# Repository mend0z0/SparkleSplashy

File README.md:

## Latest update

``
Latest update, or process that is going through
``

# Project

Description...

## Category

__Home/Office Automation__

## Features

- 
- 
- 

## Tech Stack

### Hardware

- **MCU:** ATSAM4SD16BA
- **Connection:** 
- **PCB Layers:** 4Layers (None-controlled Impedance)
- **CAD:** KiCAD

### Firmware

- **OS:** FreeRTOS
- **Programming Language:** C
- **IDE:** Microchip Studio

### Application

- **IDE:** Qt6
- **Operating System:** Linux/Windows
- **Device:** Laptop

### Mechanical

- **CAD:** Solid Edge
- **Printing Method:** 3D Printing

## Block Diagrams

## Screenshots

### Hardware

#### CAD View

#### 3D_View

#### Assembled Hardware

### Application

## Demo

Insert gif or link to demo, it'll be my youtube channel

## LOGO

## Author

- [@Siavash Taher Parvar](https://www.linkedin.com/in/mend0z0)

## Support

[Support Link](https://github.com/sponsors/mend0z0)

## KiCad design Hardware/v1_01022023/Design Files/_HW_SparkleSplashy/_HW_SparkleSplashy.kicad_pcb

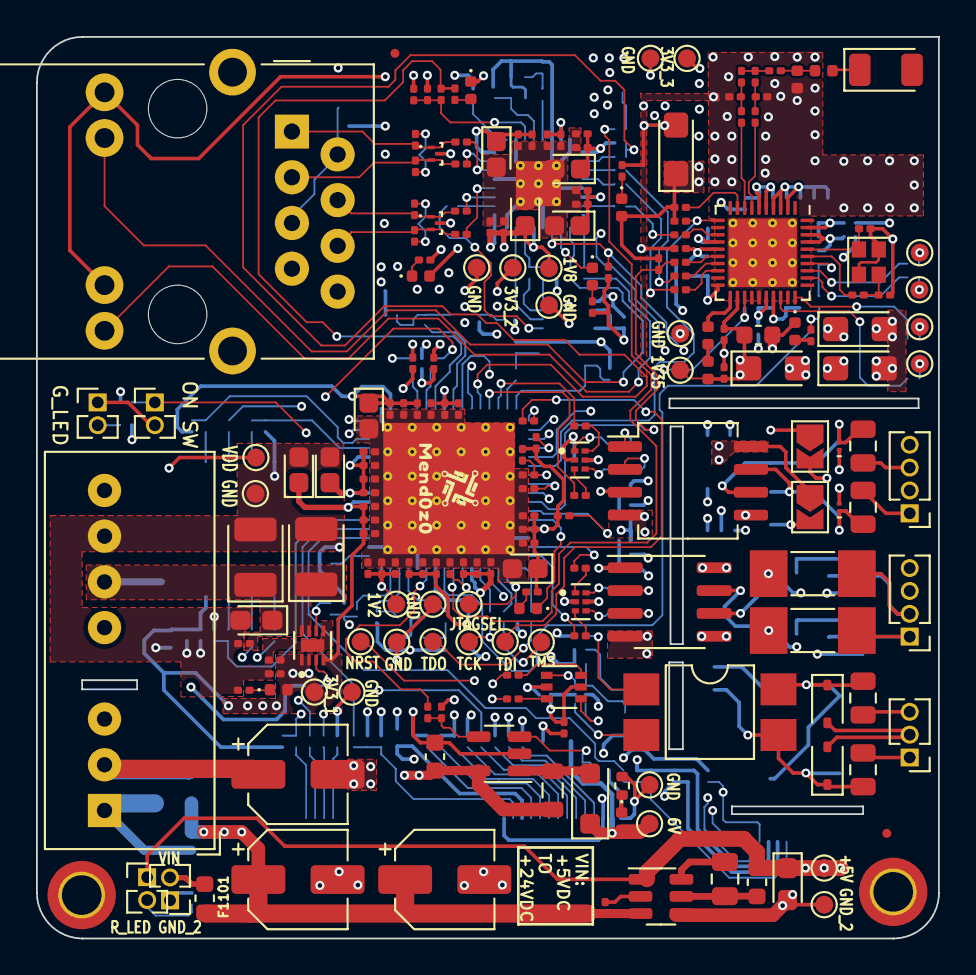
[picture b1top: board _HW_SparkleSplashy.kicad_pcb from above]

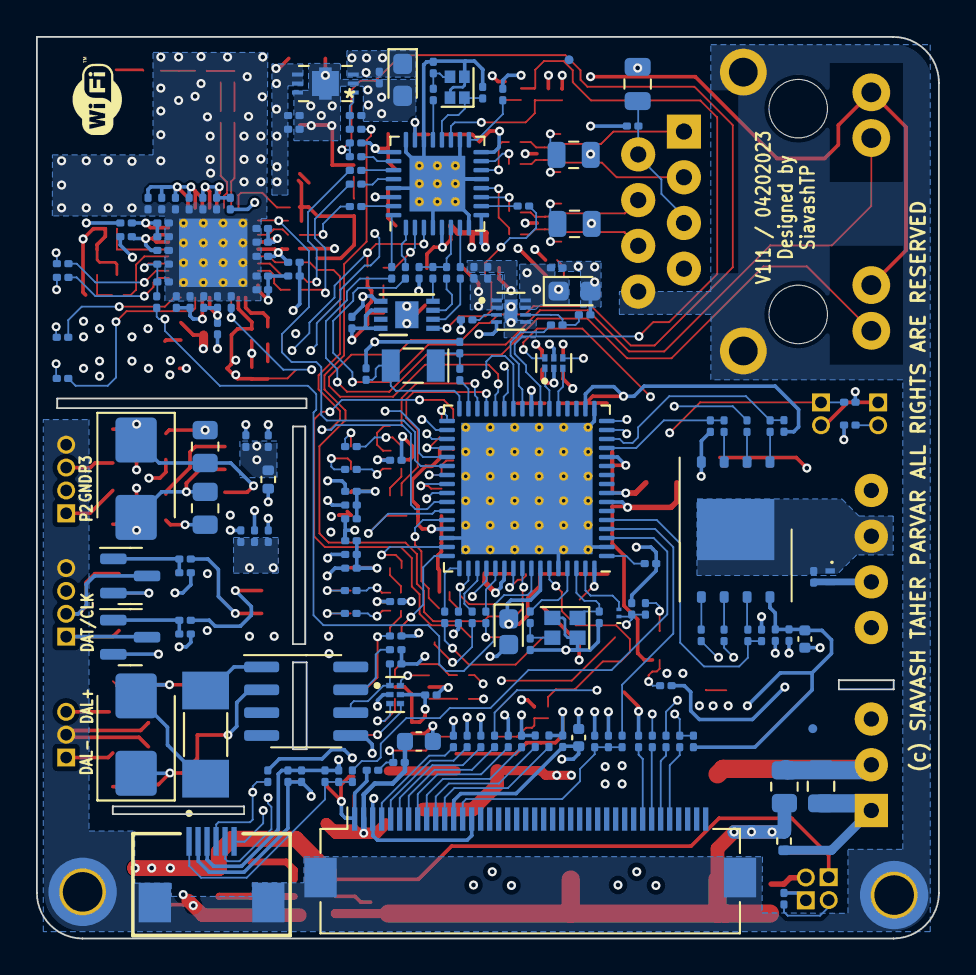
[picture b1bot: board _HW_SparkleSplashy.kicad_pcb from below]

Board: 4 copper layers, 50.1 x 50.1 mm, 381 parts (178 on the bottom side), 212 nets.

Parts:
ANT501: 2450AT18A100E; Johanson_2450AT18x100
C301, C302, C303, C304, C316, C317, C318, C324, C325, C332, C404, C408, C409, C410, C414, C504, C507, C508, C510, C520, C521, C524, C526, C529, C530, C603, C605, C803, C805, C1003, C1005, C1201, C1202, C1204, C1205: 100nF/6V3; C_0201_0603Metric
C305, C306, C307, C308, C326, C327, C328, C329, C405, C411, C412, C413, C415, C501, C514, C703: 10nF/6V3; C_0201_0603Metric
C309, C310, C311, C312: 1nF/50V; C_0201_0603Metric
C313, C314, C315, C319, C331, C417, C502, C505, C506, C509, C515, C516, C519, C525, C527, C528, C602, C801, C802, C804, C901, C902, C1001, C1002, C1004, C1206, C1207, C1208, C1209, C1210, C1211: 2u2F/6V3; C_0201_0603Metric
C320, C321, C322, C323, C406, C407, C522, C523: 12pF/50V; C_0201_0603Metric
C330: 470pF/50V; C_0201_0603Metric
C401: 10uF/50V; C_0805_2012Metric
C402, C403, C1101, C1102: 100nF/63V; C_0805_2012Metric
C416, C531, C601, C606, C702: 1uF/6V3; C_0201_0603Metric
C503, C511, C512: 1pF/50V; C_0201_0603Metric
C513, C1203, C1212: 10uF/16V; C_0603_1608Metric
C517, C518: 1p8F/50V; C_0201_0603Metric
C604, C701: 4u7F/6V3; C_0402_1005Metric
C1103: 100nF/16V; C_0201_0603Metric
D401, D402: RCLAMP0512TQTNT; 3-XDFN
D801: TISP4011H1BJR-S; D_SMB
D802, D803: ESDZV5H-1BU2; Nexperia_DSN0603-2_0.6x0.3mm_P0.4mm
D901: TISP4025H1BJR-S; D_SMB
D902, D903: SD22-01FTG; D_SOD-323
D1101: AQ1250-01ETG; SOD882
D1201: NSR01F30NXT5G; Nexperia_DSN0603-2_0.6x0.3mm_P0.4mm
D1202: 1N5819HW1-7-F; D_SOD-123F
EC1101, EC1102, EC1103: 10uF/50V; CP_Elec_5x5.3
F801, F802, F901, F902: 0805L010/24YR; Fuse_0805_2012Metric
F1101: ERB-RE1R00V; Fuse_0603_1608Metric
FD1301, FD1302, FD1303, FD1304: Fiducial_0.5mm_Mask1mm
J401: SI-60005-F; RJ45_Bel_SI-60062-F
J601: CF31401D0R0-05-NH; FPC_FH12-40S-0.5SH_1x40-1MP_P0.50mm_Horizontal
J602: F305-1A7H1-11006-E100; CONN_FPC_6POS_0.5P,BOTTOM
J801, J1001: FHDR_4POS_1.27MM; PinHeader_1x04_P1.27mm_Vertical
J901: FHDR_3POS_1.27MM; PinHeader_1x03_P1.27mm_Vertical
J1101, J1102, J1103, J1201: GRPB021VWVN-RC; PinHeader_1x02_P1.27mm_Vertical
JMP801, JMP802: JMP_2_OPEN; SolderJumper-2_P1.3mm_Open_TrianglePad1.0x1.5mm
L501: L-07C3N9SV6T; L_0402_1005Metric
L502: L-07C2N7SV6T; L_0402_1005Metric
L503, L504: WLCM0603TGB3N3TB; L_0201_0603Metric
L505: MLZ1005M2R2WT000; L_0402_1005Metric
L506: CW105550A-15NJ; L_0402_1005Metric
L1101: 4u7H; L_0603_1608Metric
L1201: 10uH; L_0805_2012Metric
LED301: ORANGE; LED_0402_1005Metric
LED302: RED; LED_0402_1005Metric
LED303, LED401: AMBER; LED_0402_1005Metric
LED1201, LED1202, LED1203: GREEN; LED_0402_1005Metric
LED1204: BLUE; LED_0402_1005Metric
MH1301, MH1302: MountingHole_2.2mm_M2_DIN965_Pad_TopBottom
Q1001, Q1002: 2N7002AQ-7; SOT-23
R301, R425, R427, R519, R601, R603, R604, R605, R606, R607, R608, R610, R611, R612, R613, R707, R708, R709, R1101, R1201, R1205, R1206, R1207, R1208, R1210: 10KR_1/20W; R_0201_0603Metric
R302, R303, R304, R305, R306, R903, R905: 3K3R_1/20W; R_0201_0603Metric
R307, R308, R309, R310, R311, R406, R506, R801, R802, R803, R804, R901, R902, R1001, R1002, R1003, R1004, R1007, R1008, R1211, R1212, R1213: 100R_1/20W; R_0201_0603Metric
R312, R313, R314, R408, R409, R426: 499R_1/20W; R_0201_0603Metric
R315, R316, R418, R424: 4K7R_1/20W; R_0201_0603Metric
R401, R410, R411, R412, R413, R501, R502, R503, R504, R505: 0R_1/20W; R_0201_0603Metric
R402, R403, R404, R405: 49R9_1/20W; R_0201_0603Metric
R407: 3K01R_1/20W; R_0201_0603Metric
R414, R415, R416, R417, R420, R421, R422, R423, R509, R510, R511, R512, R609, R614, R615, R616, R617, R701, R702, R703, R704, R705, R706: 27R4_1/20W; R_0201_0603Metric
R419, R513, R602, R618: 100KR_1/20W; R_0201_0603Metric
R507, R508, R518, R520: 1MR_1/20W; R_0201_0603Metric
R514, R515, R516, R517, R1103, R1104, R1202, R1203, R1204, R1209: 1KR_1/20W; R_0201_0603Metric
R805, R1005, R1006: 10R_1/20W; R_0201_0603Metric
R806: 1R_1/4W; R_0402_1005Metric
R807, R808: 680R_1/8W; R_0805_2012Metric
R904: 820R_1/20W; R_0201_0603Metric
R906: 4K7R_1W; R_MELF_MMB-0207
R1009, R1011: 47KR_1/20W; R_0201_0603Metric
R1010, R1012: 1KR_1W; R_MELF_MMB-0207
R1102: 0.1R_1/2W; R_0805_2012Metric
R1214: 93K1R_1/20W; R_0201_0603Metric
R1215: 24KR_1/20W; R_0201_0603Metric
R1216: 330R_1/10W; R_0402_1005Metric
TC301, TC302, TC303, TC304, TC305, TC401, TC402, TC403, TC404: 47uF/6V3; CP_EIA-1608-08_AVX-J
TC501, TC502, TC503, TC504: 22uF/6V3; CP_EIA-3216-10_Kemet-I
TC1101, TC1102: 33uF/16V; CP_EIA-3528-21_Kemet-B
TC1103, TC1201, TC1202, TC1203: 47uF/10V; CP_EIA-2012-12_Kemet-R
TP301, TP302, TP303, TP304, TP305, TP306, TP307, TP308, TP309, TP401, TP402, TP501, TP502, TP503, TP504, TP505, TP506, TP1101, TP1102, TP1103, TP1104, TP1201, TP1202, TP1203, TP1204, TP1205, TP1206, TP1207, TP1208: TestPoint_Pad_D1.0mm
U301: ATSAM4SD16BA-MU; QFN-64-1EP_9x9mm_P0.5mm_EP7.3x7.3mm_ThermalVias
U302, U801, U902, U1001: SN74LVC2G17DRYR; 6-SON
U401: KSZ8851SNLI-TR; QFN-32-1EP_5x5mm_P0.5mm_EP3.1x3.1mm_ThermalVias
U402: AT93C46DY6-YH-E; DFN-8-1EP_3x2mm_P0.5mm_EP1.3x1.5mm
U501: ATWILC1000B-MU-Y; QFN-40-1EP_5x5mm_P0.4mm_EP3.8x3.8mm_ThermalVias
U701: W25N01GVZEIG; WSON-8-1EP_8x6mm_P1.27mm_EP3.4x4.3mm
U802: MAX22028AWA+; SO-8_5.3x6.2mm_P1.27mm
U901: NC7WZ14P6X-L22347; SOT-363_SC-70-6
U903: AQY212EHA; SMDIP-4_W7.62mm
U904: VO207AT; SOIC-8_3.9x4.9mm_P1.27mm
U1002: ISO7720FDR; SOIC-8_3.9x4.9mm_P1.27mm
U1101: AP63205WU-7; SOT-23-6
U1102: PRM3W-E12-S5-S; Converter_DCDC_XP_POWER-ITxxxxxS_THT
U1201: BD33IC0WHFV-GTR; 6HVSOF
U1202: AP3012KTR-G1; SOT-23-5
U1203, U1204: LD56100DPU33R; 8-DFN
VDR1101: B72590P8200S060; R_0402_1005Metric
X301: 16MHz/10ppm; Crystal_SMD_2016-4Pin_2.0x1.6mm
X302: 32.768 kHz/5ppm; Crystal_SMD_EuroQuartz_EQ161-2Pin_3.2x1.5mm
X401: 25MHz/10ppm; Crystal_4SMD_1216_4Pin_1.2X1.6mm
X501: 26MHz/10ppm; Crystal_SMD_2016-4Pin_2.0x1.6mm

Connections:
+1V35: C501.2, C502.1, C504.1, C509.1, C510.1, C513.1, C514.1, C519.1, C524.1, C525.1, C526.1, C527.1, C529.1, L505.1, TC501.1, TP501.1, U501.2 (VDD_RF_RX_1V3), U501.3 (VDD_AMS_1V3), U501.4 (VDD_RF_TX_1V3), U501.14 (VDDC_1V3), U501.22 (VREG_BUCK), U501.27 (VDDC_1V3), U501.37 (VDD_SXDIG_1V3), U501.38 (VDD_VCO_1V3)
+5V: J1102.1, L1101.2, R806.2, R1006.2, TC1103.1, TP1103.1, U1101.1 (FB)
+6V: C1212.2, D1202.1, J601.2, LED1204.2, R1214.2, TP1201.1
/BLOCK DIAGRAM/2.4" TFT LCD + TOUCH/CTP_RESET: C601.1, J602.1, R601.2, R602.1
/BLOCK DIAGRAM/2.4" TFT LCD + TOUCH/TFT_CLK: J601.35, R616.2
/BLOCK DIAGRAM/2.4" TFT LCD + TOUCH/TFT_D/C: J601.34, R615.2
/BLOCK DIAGRAM/2.4" TFT LCD + TOUCH/TFT_IM0: J601.4, R606.2
/BLOCK DIAGRAM/2.4" TFT LCD + TOUCH/TFT_IM1: J601.5, R607.2
/BLOCK DIAGRAM/2.4" TFT LCD + TOUCH/TFT_IM2: J601.6, R608.2
/BLOCK DIAGRAM/2.4" TFT LCD + TOUCH/TFT_RESET: C606.1, J601.13, R605.2, R618.1
/BLOCK DIAGRAM/2.4" TFT LCD + TOUCH/TFT_SDA: J601.7, R609.2
/BLOCK DIAGRAM/512MB SPI FLASH/CLK: R706.1, U701.6 (CLK)
/BLOCK DIAGRAM/512MB SPI FLASH/DI: R705.1, U701.5 (DI(IO0))
/BLOCK DIAGRAM/512MB SPI FLASH/DO: R704.1, U701.2 (DO(IO1))
/BLOCK DIAGRAM/512MB SPI FLASH/~CHIPSEL: R703.1, U701.1 (~CS)
/BLOCK DIAGRAM/512MB SPI FLASH/~HOLD: R702.1, U701.7 (~HOLD(IO3))
/BLOCK DIAGRAM/512MB SPI FLASH/~WP: R701.1, U701.3 (~WP(IO2))
/BLOCK DIAGRAM/+3V3_1: C301.2, C302.2, C303.2, C304.2, C305.2, C306.2, C307.2, C308.2, C309.2, C310.2, C311.2, C312.2, C331.2, C332.2, C602.2, C603.2, C604.2, C605.2, C701.2, C702.2, C703.2, C801.1, C901.1, C902.1, C1001.2, C1207.1, C1211.1, J601.12, J602.2, LED1203.2, R301.1, R313.2, R315.1, R316.1, R603.1, R604.2, R607.1, R608.1, R707.2, R805.1, R903.2, R904.2, R905.2, R1005.2, TC301.1, TC302.1, TC303.1, TC304.1, TP1207.1, U301.7 (VDDIN_3V3), U301.18 (VDDIO_3V3), U301.45 (VDDIO_3V3), U301.58 (VDDIO_3V3), U302.5 (VCC), U701.8 (VCC), U801.5 (VCC), U901.5 (VCC), U902.5 (VCC), U1001.5 (VCC), U1204.1 (VOUT), U1204.2 (VOUT), U1204.4 (FB)
/BLOCK DIAGRAM/+3V3_2: C404.1, C405.1, C409.1, C410.1, C412.1, C413.1, C417.1, C1206.1, C1210.1, J401.L1 (GA), J401.L3 (YA), LED1202.2, R401.1, R418.2, R424.1, R426.2, R427.1, TC401.1, TC403.1, TC404.1, TP1205.1, U401.16 (VDD_A3.3), U401.25 (VDD_IO), U401.30 (VDD_IO), U402.6 (ORG), U402.8 (VCC), U1203.1 (VOUT), U1203.2 (VOUT), U1203.4 (FB)
/BLOCK DIAGRAM/+3V3_3: C1208.1, C1209.1, LED1201.2, R501.1, R502.1, R503.1, R504.1, R505.1, R507.1, R518.1, R520.1, TC502.1, TC503.1, TC504.1, TP1203.1, U1201.1 (VO), U1201.2 (FB)
/BLOCK DIAGRAM/ATWIL_EN: R508.1, U301.26 (PA26/PGMD14), U501.23 (CHIP_EN)
/BLOCK DIAGRAM/ATWIL_IRNQ: R518.2, U301.38 (PA28), U501.11 (GPIO2/IRQN)
/BLOCK DIAGRAM/ATWIL_~CS: R509.2, R520.2, U301.42 (PA30)
/BLOCK DIAGRAM/ATWIL_~RST: R312.2, R519.1, U301.57 (DDP/PB11)
/BLOCK DIAGRAM/CTP_INT: J602.4, R604.1, U301.37 (PA27/PGMD15)
/BLOCK DIAGRAM/CTP_~RST: R601.1, U301.3 (PB0/AD4)
/BLOCK DIAGRAM/DALI_RX: R901.1, U301.35 (PA5/PGMRDY)
/BLOCK DIAGRAM/DALI_TX: R902.1, U301.34 (PA6/PGMNOE)
/BLOCK DIAGRAM/DMX_RX: R801.1, U301.30 (PA9/PGMM1)
/BLOCK DIAGRAM/DMX_TX: R802.1, U301.29 (PA10/PGMM2)
/BLOCK DIAGRAM/ETHERNET CONTROLLER/KSZ_1V8_OUT: C408.1, C411.1, C414.1, C415.1, TC402.1, TP401.1, U401.5 (VDD_CO1.8), U401.9 (VDD_A1.8), U401.23 (VDD_D1.8)
/BLOCK DIAGRAM/ETHERNET CONTROLLER/KSZ_CSN: R420.1, U401.26 (CSN)
/BLOCK DIAGRAM/ETHERNET CONTROLLER/KSZ_ISET: R407.2, U401.17 (ISET)
/BLOCK DIAGRAM/ETHERNET CONTROLLER/KSZ_LED0: J401.L2 (GK), R408.1
/BLOCK DIAGRAM/ETHERNET CONTROLLER/KSZ_LED1: J401.L4 (YK), R409.1
/BLOCK DIAGRAM/ETHERNET CONTROLLER/KSZ_RSTN: C416.1, R419.1, R425.2, U401.19 (RSTN)
/BLOCK DIAGRAM/ETHERNET CONTROLLER/KSZ_SCK: R423.1, U401.28 (SCLK)
/BLOCK DIAGRAM/ETHERNET CONTROLLER/KSZ_SI: R422.1, U401.31 (SI)
/BLOCK DIAGRAM/ETHERNET CONTROLLER/KSZ_SO: R421.1, U401.27 (SO)
/BLOCK DIAGRAM/ETHERNET CONTROLLER/KSZ_XTAL1: C406.2, U401.20 (X1), X401.1
/BLOCK DIAGRAM/ETHERNET CONTROLLER/KSZ_XTAL2: R406.2, U401.21 (X2)
/BLOCK DIAGRAM/I2C_SCL: J602.5, R315.2, U301.36 (PA4/PGMNCMD)
/BLOCK DIAGRAM/I2C_SDA: J602.6, R316.2, U301.43 (PA3)
/BLOCK DIAGRAM/ISOLATED DALI/DALI_+: F901.2, J901.3
/BLOCK DIAGRAM/ISOLATED DALI/DALI_-: F902.2, J901.1
/BLOCK DIAGRAM/ISOLATED DALI/DALI_BUFF_1A: R903.1, U902.1 (1A), U904.6 (C)
/BLOCK DIAGRAM/ISOLATED DALI/DALI_BUFF_1Y: R901.2, U901.6 (1Y)
/BLOCK DIAGRAM/ISOLATED DALI/DALI_BUFF_2A: R902.2, U901.3 (2A)
/BLOCK DIAGRAM/ISOLATED DALI/DALI_BUFF_2Y: U902.4 (2Y), U903.2
/BLOCK DIAGRAM/ISOLATED DCDC CONVERTER/AP05_BST: C1102.1, U1101.6 (BST)
/BLOCK DIAGRAM/ISOLATED DCDC CONVERTER/AP05_EN: R1101.2, U1101.2 (EN)
/BLOCK DIAGRAM/ISOLATED DCDC CONVERTER/AP05_SW: C1102.2, L1101.1, U1101.5 (SW)
/BLOCK DIAGRAM/ISOLATED DMX/DMX_BUFF_1A: R803.1, U801.1 (1A)
/BLOCK DIAGRAM/ISOLATED DMX/DMX_BUFF_1Y: R801.2, U801.6 (1Y)
/BLOCK DIAGRAM/ISOLATED DMX/DMX_BUFF_2A: R802.2, U801.3 (2A)
/BLOCK DIAGRAM/ISOLATED DMX/DMX_BUFF_2Y: R804.1, U801.4 (2Y)
/BLOCK DIAGRAM/ISOLATED DMX/MAX22028_A: D801.1, D803.2, F802.1, R808.2, U802.6 (A)
/BLOCK DIAGRAM/ISOLATED DMX/MAX22028_B: D801.2, D802.1, F801.1, R807.1, U802.7 (B)
/BLOCK DIAGRAM/ISOLATED DMX/MAX22028_RXD: R803.2, U802.1 (RXD)
/BLOCK DIAGRAM/ISOLATED DMX/MAX22028_TXD: R804.2, U802.2 (TXD)
/BLOCK DIAGRAM/ISOLATED DMX/MAX22028_VDDA: C802.2, C803.2, R805.2, U802.3 (VDDA)
/BLOCK DIAGRAM/ISOLATED DMX/MAX22028_VDDB: C804.1, C805.1, JMP801.1, R806.1, U802.8 (VDDB)
/BLOCK DIAGRAM/ISOLATED DMX/XLR_PIN2: F801.2, J801.1
/BLOCK DIAGRAM/ISOLATED DMX/XLR_PIN3: F802.2, J801.3
/BLOCK DIAGRAM/ISOLATED RGB CHIP/ISO7720_INA: R1003.2, U1002.2 (INA)
/BLOCK DIAGRAM/ISOLATED RGB CHIP/ISO7720_INB: R1004.2, U1002.3 (INB)
/BLOCK DIAGRAM/ISOLATED RGB CHIP/ISO7720_VCC1: C1002.2, C1003.2, R1005.1, U1002.1 (VCC1)
/BLOCK DIAGRAM/ISOLATED RGB CHIP/ISO7720_VCC2: C1004.1, C1005.1, R1006.1, U1002.8 (VCC2)
/BLOCK DIAGRAM/ISOLATED RGB CHIP/RGB_BUFF_1A: R1002.2, U1001.3 (2A)
/BLOCK DIAGRAM/ISOLATED RGB CHIP/RGB_BUFF_1Y: R1004.1, U1001.4 (2Y)
/BLOCK DIAGRAM/ISOLATED RGB CHIP/RGB_BUFF_2A: R1001.2, U1001.1 (1A)
/BLOCK DIAGRAM/ISOLATED RGB CHIP/RGB_BUFF_2Y: R1003.1, U1001.6 (1Y)
/BLOCK DIAGRAM/ISOLATED RGB CHIP/RGB_DATA/CLK_1: J1001.1, Q1001.3, R1010.1
/BLOCK DIAGRAM/ISOLATED RGB CHIP/RGB_DATA/CLK_2: J1001.2, Q1002.3, R1012.1
/BLOCK DIAGRAM/KSZ_INTRN: R424.2, U301.15 (PA23/PGMD11), U401.3 (INTRN)
/BLOCK DIAGRAM/KSZ_PME: LED401.1, U301.16 (PA20/PGMD8/AD3), U401.2 (PME)
/BLOCK DIAGRAM/KSZ_~CS: R420.2, R427.2, U301.28 (PA11/PGMM3)
/BLOCK DIAGRAM/KSZ_~RST: R314.2, R425.1, U301.23 (PA24/PGMD12)
/BLOCK DIAGRAM/LDO REGULATORS/AP_FB: R1214.1, R1215.2, U1202.3 (FB)
/BLOCK DIAGRAM/LDO REGULATORS/AP_SW: D1202.2, L1201.2, U1202.1 (SW)
/BLOCK DIAGRAM/LDO REGULATORS/AP_~SHDN: R1204.2, R1206.1, U1202.4 (~SHDN)
/BLOCK DIAGRAM/LDO REGULATORS/ATWIL_PWR_EN: R1203.1, U301.56 (DDM/PB10)
/BLOCK DIAGRAM/LDO REGULATORS/BD33_EN: R1203.2, R1207.1, U1201.4 (EN)
/BLOCK DIAGRAM/LDO REGULATORS/BKL_EN: R1204.1, U301.59 (PB13/DAC0)
/BLOCK DIAGRAM/LDO REGULATORS/KSZ_PWR_EN: R1202.1, U301.25 (PA25/PGMD13)
/BLOCK DIAGRAM/LDO REGULATORS/LD56_1_EN: R1209.1, U1204.6 (EN)
/BLOCK DIAGRAM/LDO REGULATORS/LD56_1_LCON: R1205.2, U1204.3 (LCON)
/BLOCK DIAGRAM/LDO REGULATORS/LD56_2_EN: R1202.2, R1208.1, U1203.6 (EN)
/BLOCK DIAGRAM/LDO REGULATORS/LD56_2_LCON: R1201.2, U1203.3 (LCON)
/BLOCK DIAGRAM/LDO REGULATORS/PWR_EN: D1201.2, U301.63 (PB14/DAC1)
/BLOCK DIAGRAM/MCU_ATSAM4SD/MCU_ADVREF: R309.2, U301.1 (ADVREF)
/BLOCK DIAGRAM/MCU_ATSAM4SD/MCU_ERASE: R302.2, U301.55 (ERASE/PB12)
/BLOCK DIAGRAM/MCU_ATSAM4SD/MCU_JTAGSEL: R307.2, TP306.1, U301.50 (JTAGSEL)
/BLOCK DIAGRAM/MCU_ATSAM4SD/MCU_NRST: C324.2, R301.2, TP307.1, U301.39 (NRST)
/BLOCK DIAGRAM/MCU_ATSAM4SD/MCU_SPI_CLK: U301.21 (PA14/PGMD2), U302.3 (2A)
/BLOCK DIAGRAM/MCU_ATSAM4SD/MCU_SPI_SDO: U301.22 (PA13/PGMD1), U302.1 (1A)
/BLOCK DIAGRAM/MCU_ATSAM4SD/MCU_TCK: R305.2, U301.53 (TCK/SWCLK/PB7)
/BLOCK DIAGRAM/MCU_ATSAM4SD/MCU_TDI: R303.2, U301.33 (TDI/PB4)
/BLOCK DIAGRAM/MCU_ATSAM4SD/MCU_TDO: R304.2, U301.49 (TDO/TRACESWO/PB5)
/BLOCK DIAGRAM/MCU_ATSAM4SD/MCU_TMS: R306.2, U301.51 (TMS/SWDIO/PB6)
/BLOCK DIAGRAM/MCU_ATSAM4SD/MCU_TST: R308.2, U301.40 (TST)
/BLOCK DIAGRAM/MCU_ATSAM4SD/MCU_VOUT_1V2: C313.2, C314.2, C315.2, C316.2, C317.2, C318.2, C319.2, C325.2, C326.2, C327.2, C328.2, C329.2, C330.2, TC305.1, TP308.1, U301.8 (VDDOUT_1V2), U301.12 (VDDCORE_1V2), U301.24 (VDDCORE_1V2), U301.54 (VDDCORE_1V2), U301.64 (VDDPLL_1V2)
/BLOCK DIAGRAM/MCU_ATSAM4SD/MCU_XIN: C320.2, U301.62 (XIN/PGMCK/PB9), X301.1
/BLOCK DIAGRAM/MCU_ATSAM4SD/MCU_XIN_32: C322.2, U301.32 (PA7/XIN32/PGMNVALID), X302.2
/BLOCK DIAGRAM/MCU_ATSAM4SD/MCU_XOUT: R310.2, U301.61 (XOUT/PB8)
/BLOCK DIAGRAM/MCU_ATSAM4SD/MCU_XOUT_32: R311.2, U301.31 (PA8/XOUT32/PGMM0)
/BLOCK DIAGRAM/MCU_ATSAM4SD/PGMR_TCK: R305.1, TP304.1
/BLOCK DIAGRAM/MCU_ATSAM4SD/PGMR_TDI: R303.1, TP302.1
/BLOCK DIAGRAM/MCU_ATSAM4SD/PGMR_TDO: R304.1, TP303.1
/BLOCK DIAGRAM/MCU_ATSAM4SD/PGMR_TMS: R306.1, TP305.1
/BLOCK DIAGRAM/MSPI_CLK: R423.2, R512.2, R616.1, R706.2, U302.4 (2Y)
/BLOCK DIAGRAM/MSPI_DI: R421.2, R510.2, R704.2, U301.27 (PA12/PGMD0)
/BLOCK DIAGRAM/MSPI_DO: R422.2, R511.2, R609.1, R705.2, U302.6 (1Y)
/BLOCK DIAGRAM/RGB_1_SIG: R1002.1, U301.48 (PA0/PGMEN0)
/BLOCK DIAGRAM/RGB_2_SIG: R1001.1, U301.47 (PA1/PGMEN1)
/BLOCK DIAGRAM/TFT_DC: R615.1, U301.41 (PA29)
/BLOCK DIAGRAM/TFT_~CS: R603.2, R617.1, U301.52 (PA31)
/BLOCK DIAGRAM/TFT_~RST: R605.1, U301.4 (PB1/AD5)
/BLOCK DIAGRAM/W25N_~CS: R703.2, R707.1, U301.14 (PA22/PGMD10/AD9)
/BLOCK DIAGRAM/W25N_~HOLD: R702.2, R709.1, U301.5 (PB2/AD6)
/BLOCK DIAGRAM/W25N_~WP: R701.2, R708.1, U301.13 (PA19/PGMD7/AD2)
/BLOCK DIAGRAM/WIFI TXRX/ATWIL_RXD: R516.1, U501.28 (GPIO3)
/BLOCK DIAGRAM/WIFI TXRX/ATWIL_SPI_CFG: R507.2, U501.9 (~SDIO_SPI_CFG)
/BLOCK DIAGRAM/WIFI TXRX/ATWIL_TXD: R517.1, U501.30 (GPIO5)
/BLOCK DIAGRAM/WIFI TXRX/ATWIL_TX_N: C518.2, U501.8 (RFION)
/BLOCK DIAGRAM/WIFI TXRX/ATWIL_TX_P: C517.2, U501.7 (RFIOP)
/BLOCK DIAGRAM/WIFI TXRX/ATWIL_VBATT: C505.1, C507.1, R501.2, U501.20 (VBATT_BUCK_3V3)
/BLOCK DIAGRAM/WIFI TXRX/ATWIL_VBATT_BUCK: C506.1, C508.1, R502.2, U501.5 (VDD_BATT_PPA_3V3), U501.6 (VDD_BATT_PA_3V3)
/BLOCK DIAGRAM/WIFI TXRX/ATWIL_VDDIO: C515.1, C516.1, C520.1, C521.1, R503.2, R504.2, U501.15 (VDDIO_3V3), U501.26 (VDDIO_3V3)
/BLOCK DIAGRAM/WIFI TXRX/ATWIL_VDDIO_A: C528.1, C530.1, R505.2, U501.39 (VDDIO_A_3V3)
/BLOCK DIAGRAM/WIFI TXRX/ATWIL_VSW: L506.2, U501.21 (VSW)
/BLOCK DIAGRAM/WIFI TXRX/ATWIL_XO_N: R506.2, U501.35 (XO_N)
/BLOCK DIAGRAM/WIFI TXRX/ATWIL_XO_P: C522.2, U501.36 (XO_P), X501.1
Earth: D902.2, D903.2, J401.8 (SHIELD), J401.SH (SHIELD), J601.MP, J602.S1, J602.S2, J801.4, J901.2, J1001.4, MH1301.1, MH1302.1
GND1: C301.1, C302.1, C303.1, C304.1, C305.1, C306.1, C307.1, C308.1, C309.1, C310.1, C311.1, C312.1, C313.1, C314.1, C315.1, C316.1, C317.1, C318.1, C319.1, C320.1, C321.1, C322.1, C323.1, C324.1, C325.1, C326.1, C327.1, C328.1, C329.1, C330.1, C331.1, C332.1, C401.2, C402.2, C403.2, C404.2, C405.2, C406.1, C407.1, C408.2, C409.2, C410.2, C411.2, C412.2, C413.2, C414.2, C415.2, C416.2, C417.2, C501.1, C502.2, C504.2, C505.2, C506.2, C507.2, C508.2, C509.2, C510.2, C512.1, C513.2, C514.2, C515.2, C516.2, C519.2, C520.2, C521.2, C522.1, C523.1, C524.2, C525.2, C526.2, C527.2, C528.2, C529.2, C530.2, C531.2, C601.2, C602.1, C603.1, C604.1, C605.1, C606.2, C701.1, C702.1, C703.1, C801.2, C802.1, C803.1, C901.2, C902.2, C1001.1, C1002.1, C1003.1, C1103.2, C1201.2, C1202.2, C1203.1, C1204.2, C1205.1, C1206.2, C1207.2, C1208.2, C1209.2, C1210.2, C1211.2, C1212.1, D401.3 (GND), D402.3 (GND), D1101.1, J601.1, J601.3, J601.14, J602.3, L502.2, L503.1, LED301.1, LED303.1, R302.1, R307.1, R308.1, R309.1, R407.1, R419.2, R508.2, R513.2, R602.2, R606.1, R610.1, R611.1, R612.1, R613.1, R614.1, R618.2, R708.2, R709.2, R1104.1, R1206.2, R1207.2, R1208.2, R1210.2, R1211.1, R1212.1, R1213.1, R1215.1, R1216.1, TC301.2, TC302.2, TC303.2, TC304.2, TC305.2, TC401.2, TC402.2, TC403.2, TC404.2, TC501.2, TC502.2, TC503.2, TC504.2, TC1101.2, TC1102.2, TC1201.2, TC1202.2, TC1203.2, TP301.1, TP309.1, TP402.1, TP502.1, TP1102.1, TP1202.1, TP1204.1, TP1206.1, TP1208.1, U301.2 (GND), U301.17 (GND), U301.46 (GND), U301.60 (GND), U301.65 (GND), U302.2 (GND), U401.4 (DGND), U401.8 (AGND), U401.13 (AGND), U401.18 (AGND), U401.22 (DGND), U401.24 (DGND), U401.29 (DGND), U401.33 (DGND), U402.5 (GND), U402.9 (GND), U501.25 (TEST_MODE), U501.41 (VSS), U701.4 (GND), U701.9 (GND), U801.2 (GND), U802.4 (GNDA), U901.2 (GND), U902.2 (GND), U904.5 (E), U1001.2 (GND), U1002.4 (GND1), U1102.7 (0V), U1201.3 (GND), U1201.5 (N.C_(GND)), U1201.7 (GND), U1202.2 (GND), U1203.5 (GND), U1203.9 (GND), U1204.5 (GND), U1204.9 (GND), X301.2, X301.4, X401.2, X401.4, X501.2, X501.4
GND2: C804.2, C805.2, C1004.2, C1005.2, C1101.1, D802.2, D803.1, EC1101.2, EC1102.2, EC1103.2, J801.2, J1001.3, J1101.1, JMP802.2, Q1001.2, Q1002.2, R1009.1, R1011.1, R1103.1, TC1103.2, TP1104.1, U802.5 (GNDB), U1002.5 (GND2), U1101.4 (GND), U1102.1 (GND), VDR1101.1
unnamed: ANT501.1, L501.1
unnamed: C321.2, R310.1, X301.3
unnamed: C323.2, R311.1, X302.1
unnamed: C401.1, J401.2 (CT), J401.5 (CT), R401.2
unnamed: C402.1, R402.2, R403.2
unnamed: C403.1, R404.2, R405.2
unnamed: C407.2, R406.1, X401.3
unnamed: C503.1, L501.2, L502.1
unnamed: C503.2, C511.1, L504.1
unnamed: C511.2, C517.1, L503.2
unnamed: C512.2, C518.1, L504.2
unnamed: C523.2, R506.1, X501.3
unnamed: C1205.2, D1201.1, J1201.1, R1209.2, R1210.1
unnamed: D401.1 (CH1), J401.1 (TD+), R405.1, R410.1
unnamed: D401.2 (CH2), J401.3 (TD-), R404.1, R411.1
unnamed: D402.1 (CH1), J401.4 (RD+), R403.1, R412.1
unnamed: D402.2 (CH2), J401.6 (RD-), R402.1, R413.1
unnamed: D901.2, D902.1, F901.1, R906.2, U903.4
unnamed: F1101.1, J1101.2
unnamed: J601.8, R610.2
unnamed: J601.9, R611.2
unnamed: J601.10, R612.2
unnamed: J601.11, R613.2
unnamed: J601.33, R614.2
unnamed: J601.36, R617.2
unnamed: J1102.2, R1103.2
unnamed: J1103.2, R1104.2
unnamed: JMP801.2, R807.2
unnamed: JMP802.1, R808.1
unnamed: L505.2, L506.1
unnamed: LED301.2, R312.1
unnamed: LED302.2, R313.1
unnamed: LED303.2, R314.1
unnamed: LED401.2, R426.1
unnamed: LED1201.1, R1211.2
unnamed: LED1202.1, R1212.2
unnamed: LED1203.1, R1213.2
unnamed: LED1204.1, R1216.2
unnamed: Q1001.1, R1007.2, R1009.2
unnamed: Q1002.1, R1008.2, R1011.2
unnamed: R514.2, TP503.1
unnamed: R515.2, TP504.1
unnamed: R516.2, TP505.1
unnamed: R517.2, TP506.1
unnamed: R904.1, U903.1
unnamed: LED302.1, U301.44 (PA2/PGMEN2)
unnamed: R416.1, R417.1, R418.1, U401.6 (EDD_IO)
unnamed: R414.1, U401.10 (EECS)
unnamed: R415.1, U401.7 (EESK)
unnamed: R408.2, U401.1 (LED0)
unnamed: R409.2, U401.32 (LED1)
unnamed: R413.2, U401.12 (RXM)
unnamed: R412.2, U401.11 (RXP)
unnamed: R411.2, U401.15 (TXM)
unnamed: R410.2, U401.14 (TXP)
unnamed: R414.2, U402.1 (CS)
unnamed: R416.2, U402.3 (DI)
unnamed: R417.2, U402.4 (DO)
unnamed: R415.2, U402.2 (SK)
unnamed: R515.1, U501.32 (I2C_SCL)
unnamed: R514.1, U501.33 (I2C_SDA)
unnamed: C531.1, R513.1, R519.2, U501.34 (RESETN)
unnamed: R512.1, U501.18 (SD_CMD/SPI_SCK)
unnamed: R510.1, U501.17 (SD_DAT0/SPI_TXD)
unnamed: R509.1, U501.16 (SD_DAT1/SPI_SSN)
unnamed: R511.1, U501.13 (SD_DAT2/SPI_RXD)
unnamed: U901.1 (1A), U902.6 (1Y)
unnamed: U901.4 (2Y), U902.3 (2A)
unnamed: R906.1, U904.1 (A)
unnamed: R905.1, U904.7 (B)
unnamed: D901.1, D903.1, F902.1, U903.3, U904.2 (K)
unnamed: R1007.1, U1002.7 (OUTA)
unnamed: R1008.1, U1002.6 (OUTB)
unnamed: C1101.2, EC1103.1, R1102.2, U1102.2 (VIN)
VCC: EC1101.1, EC1102.1, F1101.2, R1010.2, R1012.2, R1101.1, R1102.1, U1101.3 (VIN), VDR1101.2
VDD: C1103.1, C1201.1, C1202.1, C1203.2, C1204.1, D1101.2, J1103.1, J1201.2, L1201.1, R1201.1, R1205.1, TC1101.1, TC1102.1, TC1201.1, TC1202.1, TC1203.1, TP1101.1, U1102.6 (+VO), U1201.6 (VCC), U1202.5 (VIN), U1203.7 (VIN), U1203.8 (VIN), U1204.7 (VIN), U1204.8 (VIN)

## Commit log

2023-09-30 File restructuring
2023-12-25 some junk update
2023-12-26 Some modification in file structure
2023-12-26 Adding 3D view pic
2023-12-26 Adding Screenshots
2023-12-26 Updating the README file
2023-12-26 Updating file structure and README
2024-01-05 Updating folders and file structure
2024-01-07 Updating the library
2024-01-07 Change in directory date
2024-01-07 Updating library
2024-02-04 Exporting BOM
2024-02-04 Creating CAD folder for 3D CAD model
2024-02-04 3D CAD Mech has been created.
2024-02-04 Enclosure sides have been created!
2024-02-04 Some dimensions have been added and a 3D model has been modified
2024-02-05 Working on 3D CAD Model
2024-02-11 Uploading the BlockDiagrams
